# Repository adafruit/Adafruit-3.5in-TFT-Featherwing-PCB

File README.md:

## Adafruit 3.5in TFT LCD Display FeatherWing PCB

<a href="http://www.adafruit.com/products/3651"><br/>
Click here to purchase one from the Adafruit shop</a>

PCB files for the Adafruit 3.5in TFT LCD display FeatherWing. Format is EagleCAD schematic and board layout

For more details, check out the product page at
* https://www.adafruit.com/products/3651

### Description

Spice up your Feather project with a beautiful 3.5" touchscreen display shield with built in microSD card socket. This TFT display is 3.5" diagonal with a bright 6 white-LED backlight. You get a massive 480x320 pixels with individual 16-bit color pixel control. It has way more resolution than a black and white 128x64 display, and twice as much as our 2.4" TFT FeatherWing. As a bonus, this display comes with a resistive touchscreen attached to it already, so you can detect finger presses anywhere on the screen

This FeatherWing uses a SPI display, touchscreen and SD card socket. It works with any and all Feathers but given the large display it works best with our faster boards like the nRF52, ESP8266, ESP32, M0, M4, WICED, and Teensy. We also include an SPI resistive touchscreen controller so you only need one additional pin to add a high quality touchscreen controller. One more pin is used for an optional SD card that can be used for storing images for display.

This Wing comes fully assembled with dual sockets for your Feather to plug into. You get two sockets per pin so you can plug in wires if you want to connect to Feather pins. Alternatively, each pin has a large square pad on the PCB for direct soldering.

### License

Adafruit invests time and resources providing this open source design, please support Adafruit and open-source hardware by purchasing products from [Adafruit](https://www.adafruit.com)!

Designed by Limor Fried/Ladyada for Adafruit Industries.

Creative Commons Attribution/Share-Alike, all text above must be included in any redistribution. See license.txt for additional details.

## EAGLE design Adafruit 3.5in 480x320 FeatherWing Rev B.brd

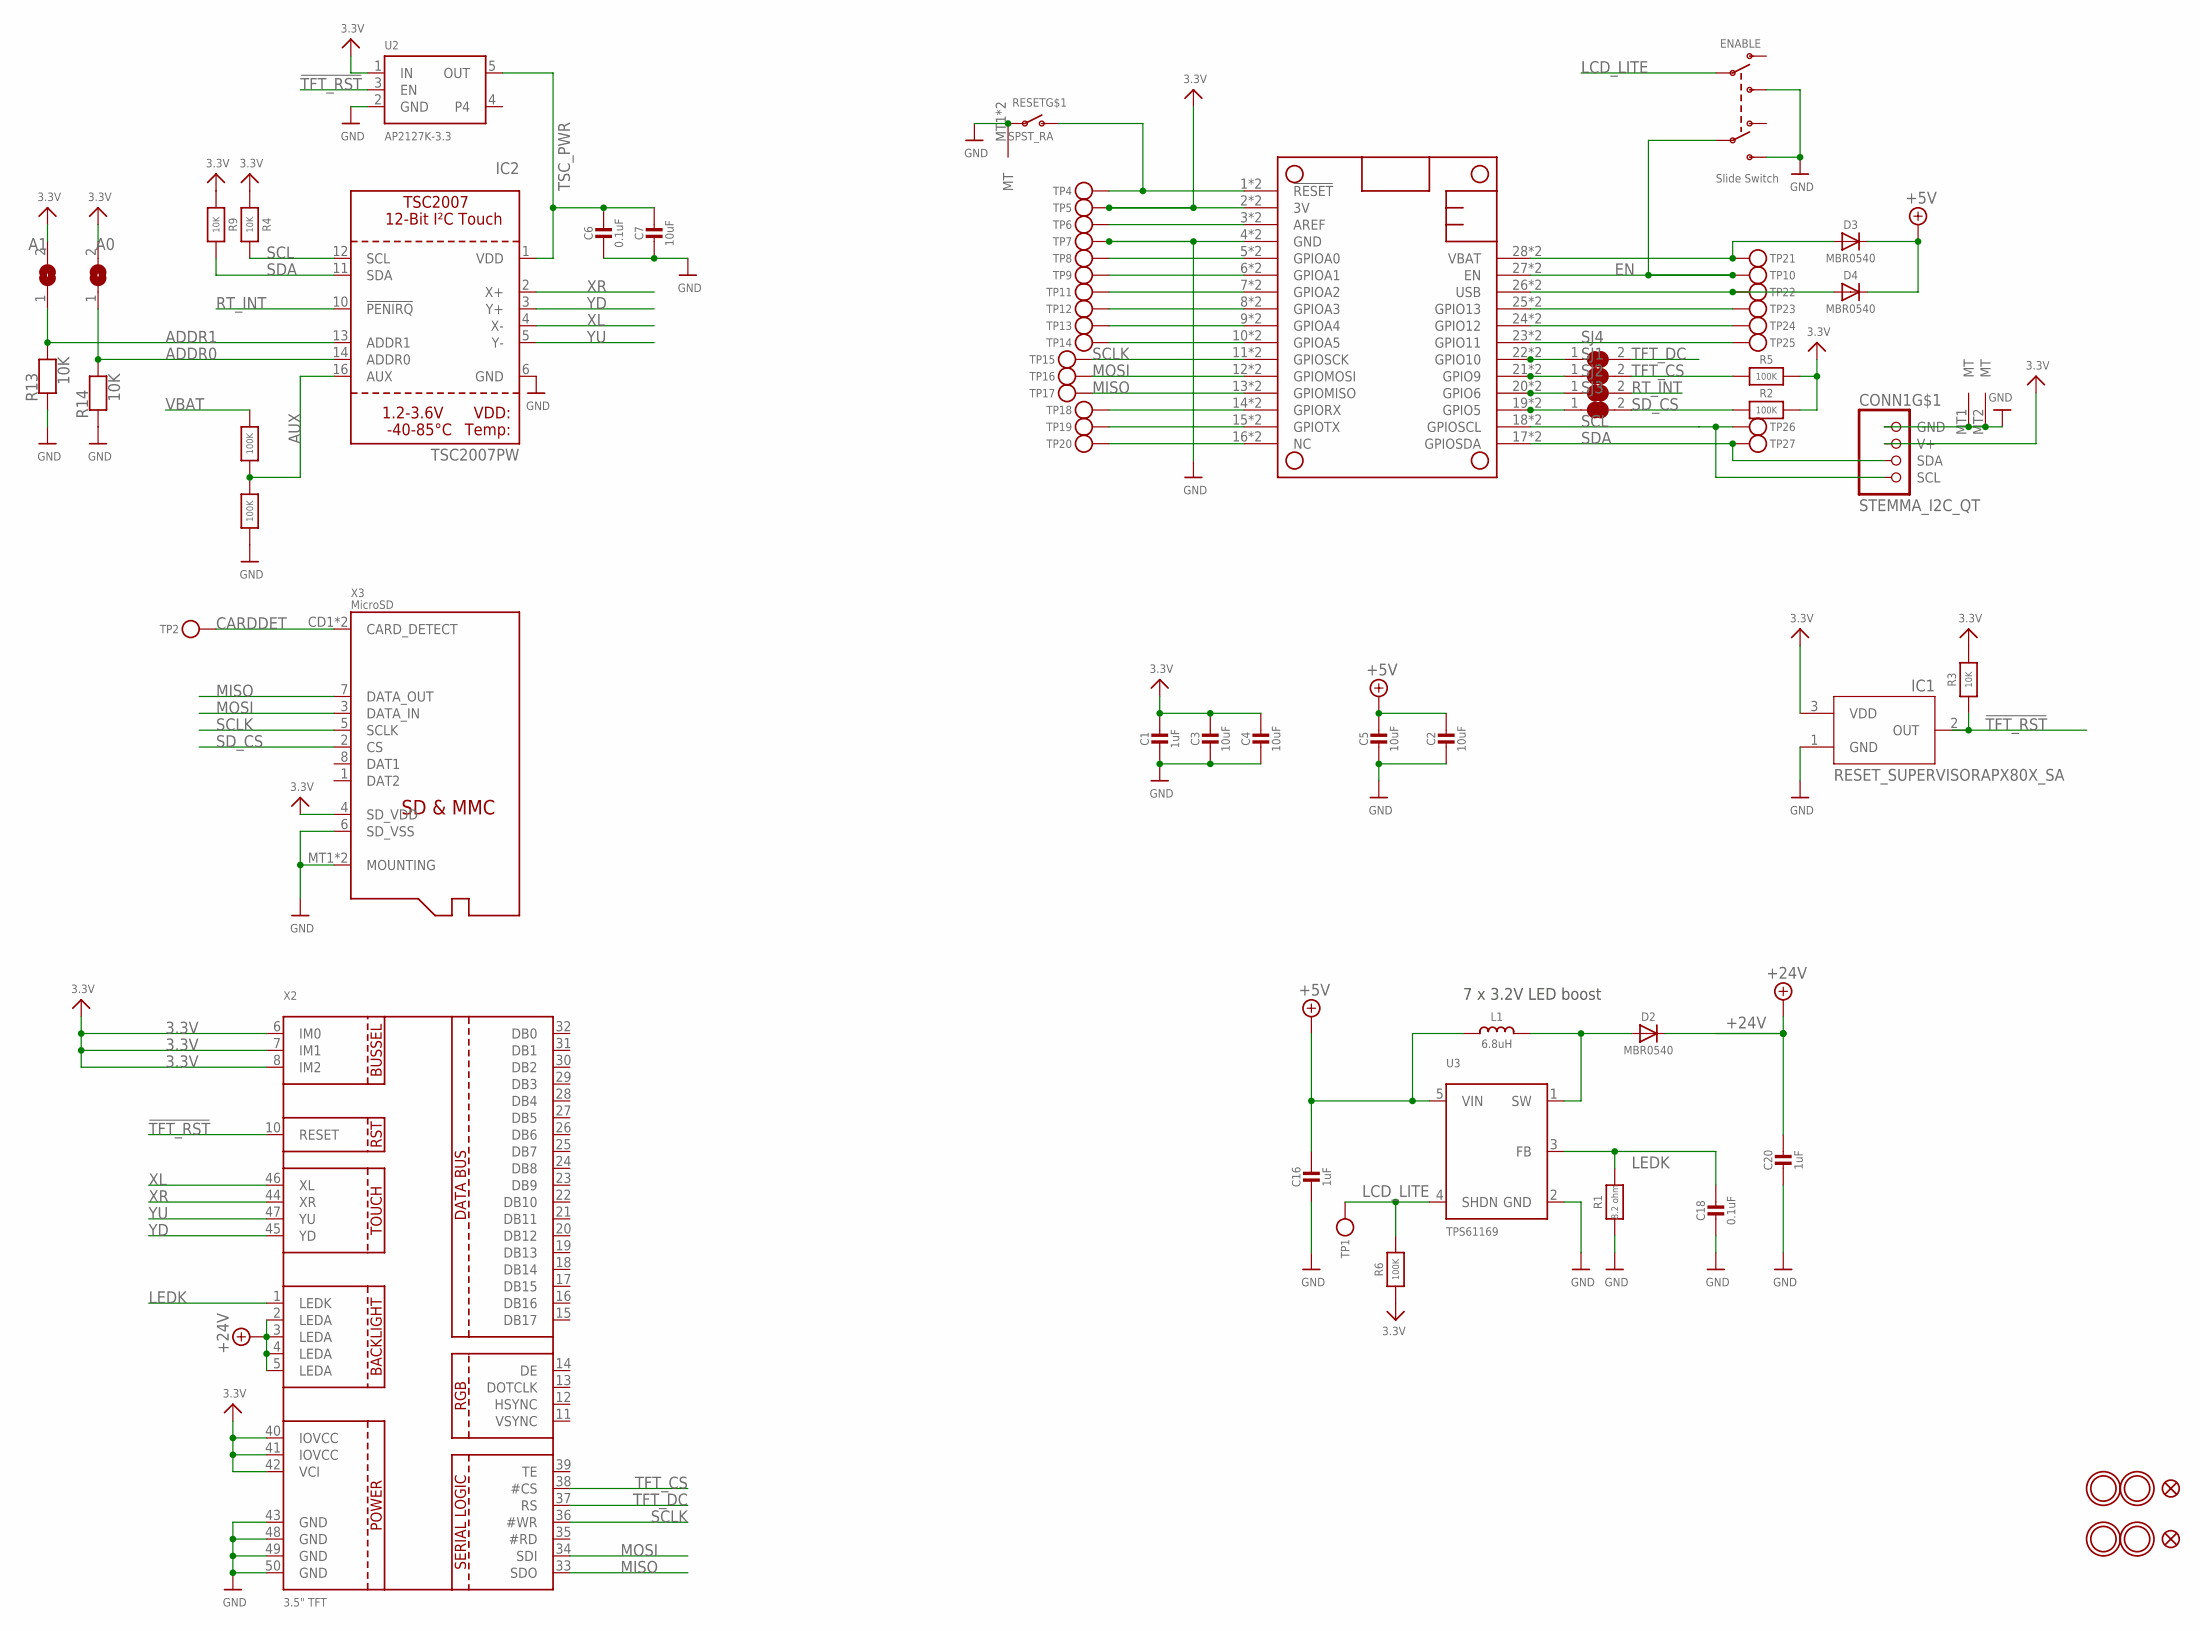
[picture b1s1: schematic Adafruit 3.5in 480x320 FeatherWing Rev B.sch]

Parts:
C1, C16, C20: 1uF; 0805-NO
C2, C3, C4, C5, C7: 10uF; 0805-NO
C6, C18: 0.1uF; 0603-NO
CONN1: STEMMA_I2C_QT; JST_SH4
D2, D3, D4: MBR0540; SOD-123
ENABLE: Slide Switch; EG1390
IC1: RESET_SUPERVISORAPX80X_SA; SOT23-WIDE
IC2: TSC2007PW; TSSOP16
ICSP_CLK1: A1; SOLDERJUMPER_ARROW_NOPASTE
ICSP_CLK2: A0; SOLDERJUMPER_ARROW_NOPASTE
L1: 6.8uH; INDUCTOR_5X5MM_NR5040_NOTHERMALS
MS2: FEATHERWING_SMTDUAL; FEATHERWING_SMT2
R1: 8.2 ohm; 0603-NO
R2, R5, R6, R10, R11: 100K; 0603-NO
R3, R4, R9, R13, R14: 10K; 0603-NO
RESET: SPST_RA; SPST_TACTILE_RA
SJ1, SJ2, SJ3, SJ4: SOLDERJUMPER_CLOSED; SOLDERJUMPER_CLOSEDWIRE
TP1, TP2, TP4, TP5, TP6, TP7, TP8, TP9, TP10, TP11, TP12, TP13, TP14, TP15, TP16, TP17, TP18, TP19, TP20, TP21, TP22, TP23, TP24, TP25, TP26, TP27: TESTPOINTPAD2MM; TESTPOINT_PAD_2MM
U2: AP2127K-3.3; SOT23-5
U3: TPS61169; SC70-5
U$7, U$15, U$16, U$17: MOUNTINGHOLE3.0THIN; MOUNTINGHOLE_3.0_PLATEDTHIN
U$9, U$23: FIDUCIAL_1MM
X2: 3.5" TFT; TFT_3.5IN_320X480_50PIN
X3: MicroSD; MICROSD

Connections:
3.3V: C1.1, C3.1, C4.1, CONN1.2 (V+), IC1.3 (VDD), ICSP_CLK1.2, ICSP_CLK2.2, MS2.2 (3V), MS2.2' (3V), R2.2, R3.2, R4.1, R5.2, R6.1, R9.1, TP5.P$1, U2.1 (IN), X2.6 (IM0), X2.7 (IM1), X2.8 (IM2), X2.40 (IOVCC), X2.41 (IOVCC), X2.42 (VCI), X3.4 (SD_VDD)
!RESET: MS2.1 (!RESET), MS2.1' (!RESET), RESET.2 (S), TP4.P$1
!TFT_RST: IC1.2 (OUT), R3.1, U2.3 (EN), X2.10 (RESET)
+5V: C2.1, C5.1, C16.1, D3.C, D4.C, L1.P$1 (1), U3.5 (VIN)
+24V: C20.1, D2.C, X2.2 (LEDA), X2.3 (LEDA), X2.4 (LEDA), X2.5 (LEDA)
A: MS2.5 (GPIOA0), MS2.5' (GPIOA0), TP8.P$1
ADDR0: IC2.14 (ADDR0), ICSP_CLK2.1, R14.2
ADDR1: IC2.13 (ADDR1), ICSP_CLK1.1, R13.2
AREF: MS2.3 (AREF), MS2.3' (AREF), TP6.P$1
AUX: IC2.16 (AUX), R10.1, R11.2
B: MS2.6 (GPIOA1), MS2.6' (GPIOA1), TP9.P$1
C: MS2.7 (GPIOA2), MS2.7' (GPIOA2), TP11.P$1
CARDDET: TP2.P$1, X3.CD1 (CARD_DETECT), X3.CD2 (CARD_DETECT)
D: MS2.8 (GPIOA3), MS2.8' (GPIOA3), TP12.P$1
E: MS2.9 (GPIOA4), MS2.9' (GPIOA4), TP13.P$1
EN: ENABLE.P2, MS2.27 (EN), MS2.27' (EN), TP10.P$1
F: MS2.10 (GPIOA5), MS2.10' (GPIOA5), TP14.P$1
G: MS2.16 (NC), MS2.16' (NC), TP20.P$1
GND: C1.2, C2.2, C3.2, C4.2, C5.2, C6.2, C7.2, C16.2, C18.2, C20.2, CONN1.1 (GND), CONN1.MT1 (MT), CONN1.MT2 (MT), ENABLE.S1, ENABLE.S2, IC1.1 (GND), IC2.6 (GND), MS2.4 (GND), MS2.4' (GND), R1.1, R11.1, R13.1, R14.1, RESET.1, RESET.MT1 (MT), RESET.MT2 (MT), TP7.P$1, U2.2 (GND), U3.2 (GND), X2.43 (GND), X2.48 (GND), X2.49 (GND), X2.50 (GND), X3.6 (SD_VSS), X3.MT1 (MOUNTING), X3.MT2 (MOUNTING)
H: MS2.19 (GPIO5), MS2.19' (GPIO5), SJ3.1
I: MS2.20 (GPIO6), MS2.20' (GPIO6), SJ2.1
J: MS2.21 (GPIO9), MS2.21' (GPIO9), SJ1.1
K: MS2.22 (GPIO10), MS2.22' (GPIO10), SJ4.1
L: MS2.23 (GPIO11), MS2.23' (GPIO11), TP25.P$1
LCD_LITE: ENABLE.P1, R6.2, TP1.P$1, U3.4 (SHDN)
LEDK: C18.1, R1.2, U3.3 (FB), X2.1 (LEDK)
M: MS2.24 (GPIO12), MS2.24' (GPIO12), TP24.P$1
MISO: MS2.13 (GPIOMISO), MS2.13' (GPIOMISO), TP17.P$1, X2.33 (SDO), X3.7 (DATA_OUT)
MOSI: MS2.12 (GPIOMOSI), MS2.12' (GPIOMOSI), TP16.P$1, X2.34 (SDI), X3.3 (DATA_IN)
N: MS2.25 (GPIO13), MS2.25' (GPIO13), TP23.P$1
unnamed: D2.A, L1.P$2 (2), U3.1 (SW)
RT_INT: IC2.10 (!PENIRQ), SJ2.2
RX: MS2.14 (GPIORX), MS2.14' (GPIORX), TP18.P$1
SCL: CONN1.4 (SCL), IC2.12 (SCL), MS2.18 (GPIOSCL), MS2.18' (GPIOSCL), R4.2, TP26.P$1
SCLK: MS2.11 (GPIOSCK), MS2.11' (GPIOSCK), TP15.P$1, X2.36 (#WR), X3.5 (SCLK)
SDA: CONN1.3 (SDA), IC2.11 (SDA), MS2.17 (GPIOSDA), MS2.17' (GPIOSDA), R9.2, TP27.P$1
SD_CS: R2.1, SJ3.2, X3.2 (CS)
TFT_CS: R5.1, SJ1.2, X2.38 (#CS)
TFT_DC: SJ4.2, X2.37 (RS)
TSC_PWR: C6.1, C7.1, IC2.1 (VDD), U2.5 (OUT)
TX: MS2.15 (GPIOTX), MS2.15' (GPIOTX), TP19.P$1
USB: D4.A, MS2.26 (USB), MS2.26' (USB), TP22.P$1
VBAT: D3.A, MS2.28 (VBAT), MS2.28' (VBAT), R10.2, TP21.P$1
XL: IC2.4 (X-), X2.46 (XL)
XR: IC2.2 (X+), X2.44 (XR)
YD: IC2.3 (Y+), X2.45 (YD)
YU: IC2.5 (Y-), X2.47 (YU)

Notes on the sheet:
7 x 3.2V LED boost

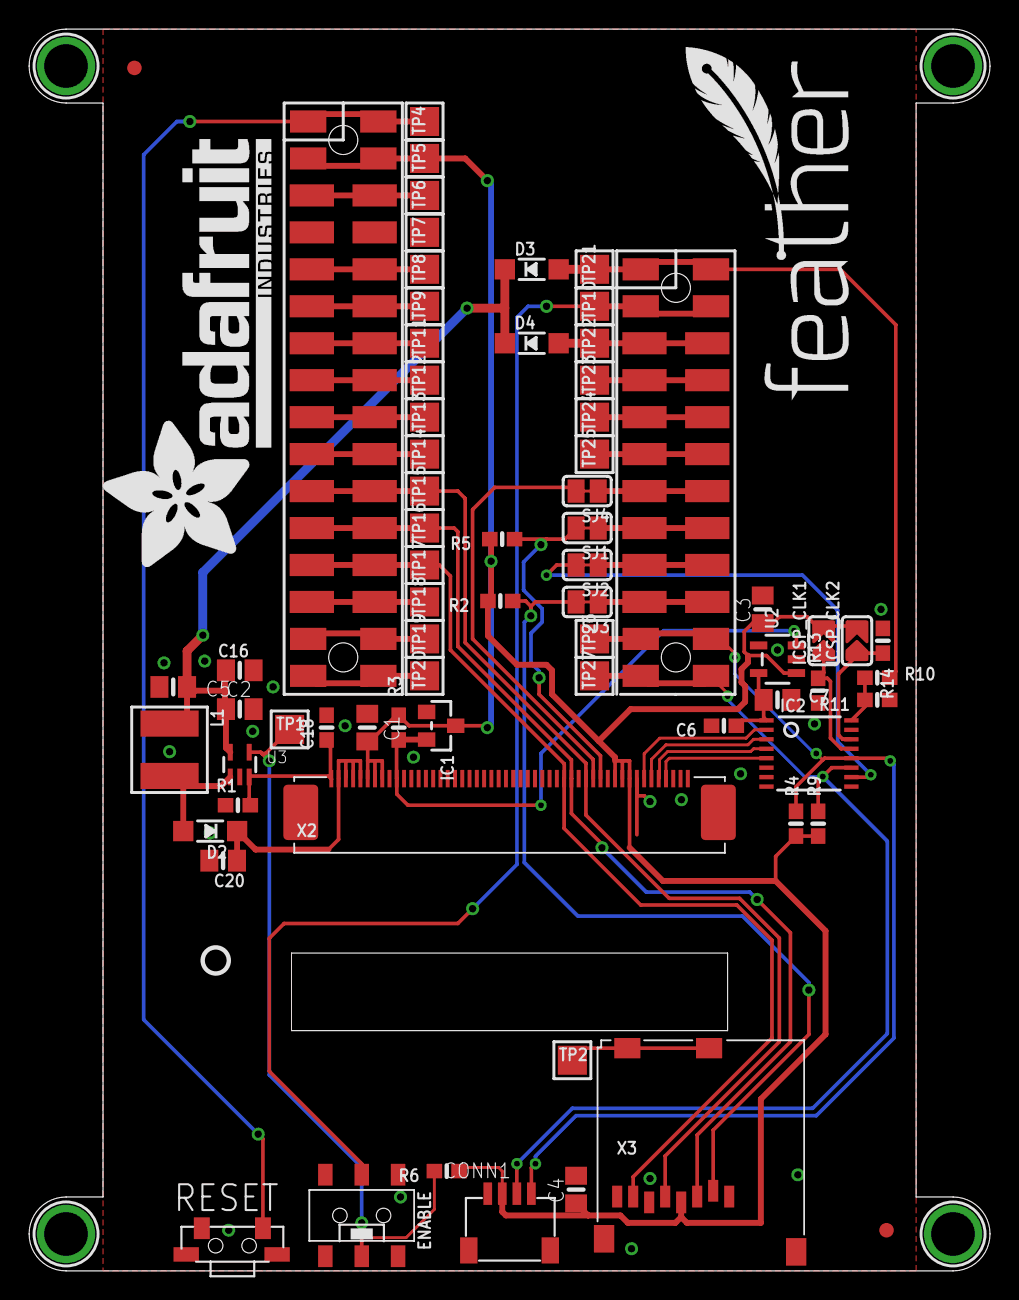
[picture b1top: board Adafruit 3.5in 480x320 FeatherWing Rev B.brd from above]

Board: 2 copper layers, 66.0 x 85.3 mm, 92 parts (1 on the bottom side), 47 nets.

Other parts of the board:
PLABEL0: PLABEL0
PLABEL1: PLABEL1
PLABEL2: PLABEL2
PLABEL3: PLABEL3
PLABEL4: PLABEL4
PLABEL5: PLABEL5
PLABEL6: PLABEL6
PLABEL7: PLABEL7
PLABEL8: PLABEL8
PLABEL9: PLABEL9
PLABEL10: PLABEL10
PLABEL11: PLABEL11
PLABEL12: PLABEL12
PLABEL13: PLABEL13
PLABEL14: PLABEL14
PLABEL15: PLABEL15
U$11: FEATHERLOGO
U$19: ADAFRUIT_TEXT_30MM
U$37: PCBFEAT-REV-040

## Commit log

2017-10-25 files
2017-10-25 read
2023-11-20 rev B files
